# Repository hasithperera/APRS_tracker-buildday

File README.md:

# APRS tracker-build day

- This project is designed as an out reach project under the WVU Amateur radio club - High altitude ballooning grand awarded Fall 2024
- The main goal was to design a system allowing users to send APRS location packets

---
## V1.1 - APRS beacon

- [Build instructions](pcb/README.md) - Partially completed
---
## Bluetooth KISS TNC - v 1.0

- Based on the interest, we added a part 2 for the build day that was developed for advanced users who needed APRS decode capabilities.
- A self powered KISS TNC PCB was designed to carry existing firmware.
	- Initial testing with APRSDroid and YAAC showed promising results
- V1 PCB for the APRS KISS TNC 

---
## Project progress

- November 2024 - Reached out to local clubs on interest and participation
- December 2024 - Basic prototype was tested 
- January 2025 - v1.1 production 
- March 2025 - Software was finalized to allow consistent operation 
- April 2025 - BT KISS TNC v1 PCB added 

*Last edited: April 09 by KE8TJE*

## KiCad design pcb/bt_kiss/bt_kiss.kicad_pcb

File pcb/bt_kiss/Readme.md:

- The Bluetooth KISS TNC implementation schematic and board designs for quick access

## Schematic 

## Program instructions

- Firmware found [here](https://raw.githubusercontent.com/mobilinkd/tnc1/arduino/images/mobilinkd-473-arduino.hex)
- Programming using the com port: `avrdude -c arduino -p m328p -P /dev/ttyUSB1 -b 57600 -U mobilinkd-473-arduino.hex`
- Programming using a USBasp: `avrdude -p m328p -c usbasp -U flash:w:<filename>.hex`

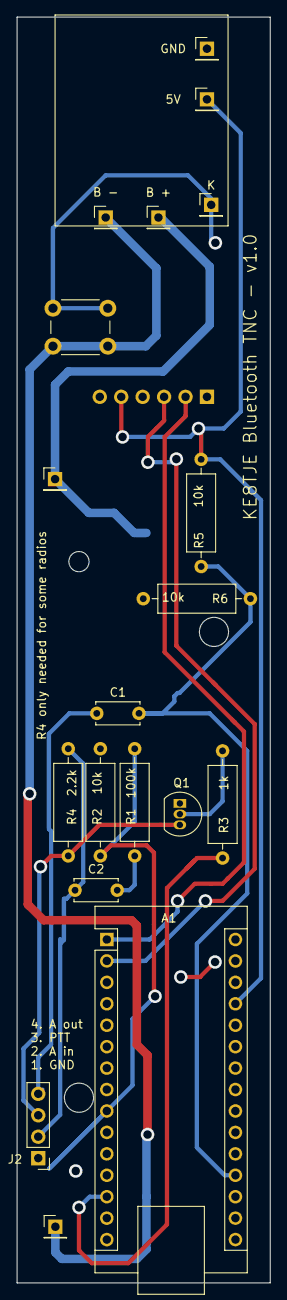
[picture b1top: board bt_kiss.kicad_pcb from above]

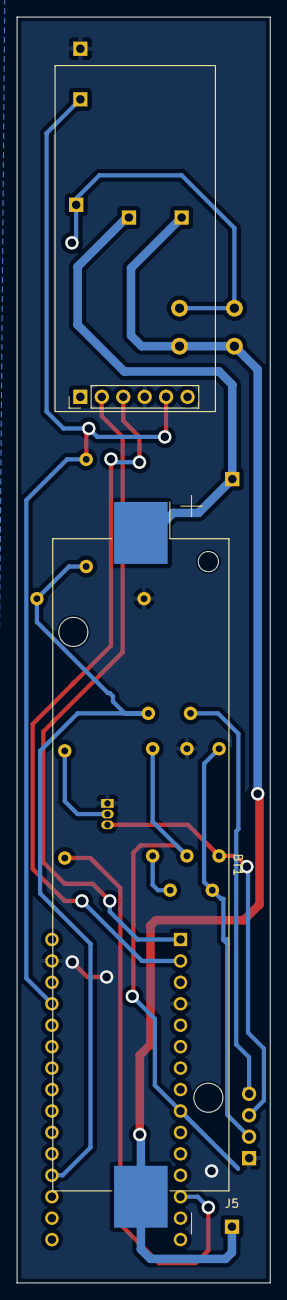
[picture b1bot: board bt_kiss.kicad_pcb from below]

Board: 2 copper layers, 30.0 x 150.0 mm, 21 parts (2 on the bottom side), 15 nets.

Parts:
5V: 5V; PinHeader_1x01_P2.54mm_Vertical
A1: Arduino_Nano_v3.x; Arduino_Nano
B +: Bat_Plus; PinHeader_1x01_P2.54mm_Vertical
B -: Bat_GND; PinHeader_1x01_P2.54mm_Vertical
BT1: Battery_Cell; BatteryHolder_Keystone_1042_1x18650
C1: 10nf; C_Disc_D5.0mm_W2.5mm_P5.00mm
C2: 100nf; C_Disc_D5.0mm_W2.5mm_P5.00mm
GND: GND; PinHeader_1x01_P2.54mm_Vertical
J1: HC-05; PinHeader_1x06_P2.54mm_Vertical
J2: to_radio; PinHeader_1x04_P2.54mm_Vertical
J4: Bat_Plus; PinHeader_1x01_P2.54mm_Vertical
J5: Bat_GND; PinHeader_1x01_P2.54mm_Vertical
K: Key; PinHeader_1x01_P2.54mm_Vertical
Q1: PN2222A; TO-92_Inline
R1: 100k; R_Axial_DIN0309_L9.0mm_D3.2mm_P12.70mm_Horizontal
R2, R5, R6: 10k; R_Axial_DIN0309_L9.0mm_D3.2mm_P12.70mm_Horizontal
R3: 1k; R_Axial_DIN0309_L9.0mm_D3.2mm_P12.70mm_Horizontal
R4: 2.2k; R_Axial_DIN0309_L9.0mm_D3.2mm_P12.70mm_Horizontal
SW1: SW_Push; SW_PUSH_6mm

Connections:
GND: A1.4 (GND), A1.29 (GND), GND.1, J1.4, J2.1, Q1.1 (E), R2.2, R6.2
unnamed: A1.19 (A0), C1.2, R5.2, R6.1
unnamed: A1.2 (D0/RX), J1.3
unnamed: A1.1 (D1/TX), J1.2
unnamed: A1.9 (D6), R1.1, R2.1
unnamed: A1.13 (D10), R3.1
unnamed: B +.1, BT1.1 (+), J4.1
unnamed: B -.1, BT1.2 (-), J5.1, SW1.2
unnamed: C2.2, R1.2
unnamed: K.1, SW1.1
unnamed: Q1.2 (B), R3.2
PTT: J2.3, Q1.3 (C), R4.1
VCC: 5V.1, A1.27 (+5V), J1.5, R5.1
audio_in: C2.1, J2.2, R4.2
audio_out: C1.1, J2.4

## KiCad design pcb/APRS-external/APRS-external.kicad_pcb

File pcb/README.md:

# PCB Design updates 

## V1.1 

---
## Build guide 

- Follow the component list below and populate the PCB with components 
- Note 2 changes:
	- the 2N2222 needs to be replaced by a BS170 MOSFET
	- Bridge the Pins **D2** and **D3** on the Arduino
- Once you have every thing soldered in connect power via the USB C connector
	- You should see the power led light up on the arduino
	- Power led on the GPS module
- Once you have confirmed power to all the components follow the programming guide 

---
## Component list

| **Symbol** | **Value**    |
| ---------- | ------------ |
| C1         | 100n         |
| C2,C3      | 4.7u         |
| C3,C4      | pol smd      |
| D1         | 1n4001       |
| Q1         | 2N2222/BS170 |
| R1         | 6.2k         |
| R2         | 2k           |
| R3         | 270          |
| R4         | 3.9k         |
| R5         | 1.2k         |
| R6-R8      | 1k           |
| R10        | 2.7k         |
| R11,R12    | 330          |

---
## Program instructions

- Open up the Arduino code provided
- to install the Aprs library go to: Tools > Manage Libraries....
	- Search for `LibAPRS` and install the library by Baris DINC
- Once you have the library installed compile the program and it should compile without errors
- Change `line 45` to add your call
### Basic radio interface testing

- Once the Arduino is properly programmed on power on the Radio will be keyed up 2 times as a test. 
	- If this step fails: check your connectors and check your MOSFET.
- To test the system indoors without GPS lock uncomment `line 30`, this will enable a simulate mode where GPS data is being. artificially provided 
- Once the second count reaches the value set in `APRS_TX_offset_utc_sec` your radio will transmit an APRS packet.
	- Radio should key down automatically
	- It has been repoted with some radios this may not happen and this was often observed when there was an extended length of cable involved
		- adding a ferrite bead would potentially solve the issue
		- if not using a separate external antenna should help
- NOTE: change the `APRS_TX_offset_utc_sec` to some random value. This is the time your specific APRS unit will transmit. Since its on simplex we don't want every one to TX at the same time. 
- once you have completed testing comment out `line 30` congratulations now you have a working APRS beacon 

if you have questions please reach out to KE8TJE

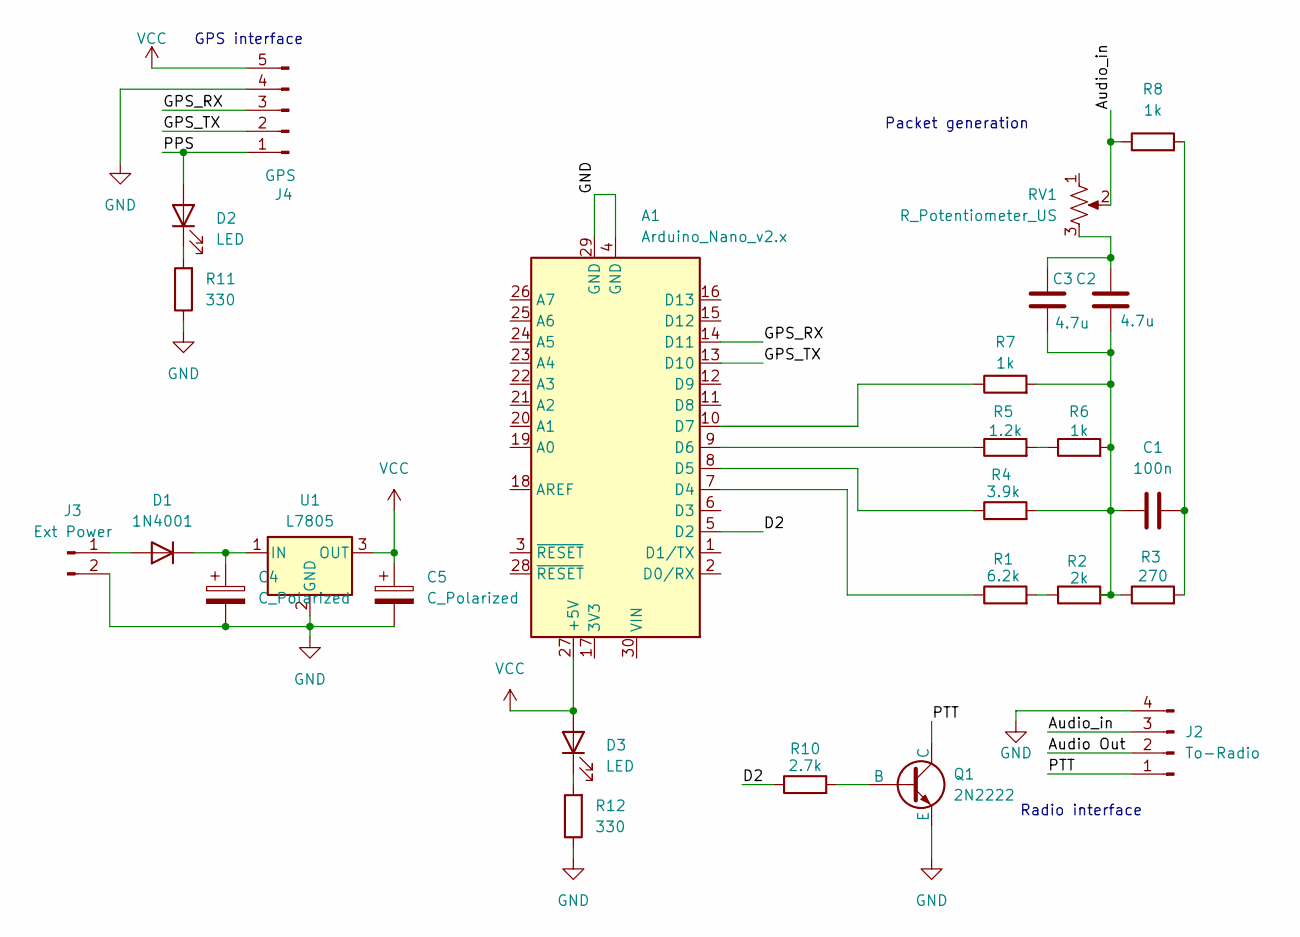
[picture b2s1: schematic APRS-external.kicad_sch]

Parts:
A1: Arduino_Nano_v2.x; Arduino_Nano
C1: 100n; D_0805_2012Metric_Pad1.15x1.40mm_HandSolder
C2, C3: 4.7u; D_0805_2012Metric_Pad1.15x1.40mm_HandSolder
C4, C5: C_Polarized; CP_Elec_4x4.5
D1: 1N4001; D_DO-41_SOD81_P10.16mm_Horizontal
D2, D3: LED; LED_D5.0mm
J2: To-Radio; PinHeader_1x04_P2.54mm_Vertical
J3: Ext Power; PinHeader_1x02_P2.54mm_Vertical
J4: GPS; PinHeader_1x05_P2.54mm_Vertical
Q1: 2N2222; TO-92_Inline_Wide
R1: 6.2k; R_Axial_DIN0207_L6.3mm_D2.5mm_P10.16mm_Horizontal
R2: 2k; R_Axial_DIN0207_L6.3mm_D2.5mm_P10.16mm_Horizontal
R3: 270; R_Axial_DIN0207_L6.3mm_D2.5mm_P10.16mm_Horizontal
R4: 3.9k; R_Axial_DIN0207_L6.3mm_D2.5mm_P10.16mm_Horizontal
R5: 1.2k; R_Axial_DIN0207_L6.3mm_D2.5mm_P10.16mm_Horizontal
R6, R7, R8: 1k; R_Axial_DIN0207_L6.3mm_D2.5mm_P10.16mm_Horizontal
R10: 2.7k; R_Axial_DIN0207_L6.3mm_D2.5mm_P10.16mm_Horizontal
R11, R12: 330; R_Axial_DIN0207_L6.3mm_D2.5mm_P10.16mm_Horizontal
RV1: R_Potentiometer_US; Potentiometer_Piher_PT-10-V05_Vertical
U1: L7805; TO-220-3_Horizontal_TabDown

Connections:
/Audio Out: J2.2
/Audio_in: J2.3, R8.1, RV1.2
/D2: A1.5 (D2), R10.1
/GPS_RX: A1.14 (D11), J4.3
/GPS_TX: A1.13 (D10), J4.2
/PPS: D2.2 (A), J4.1
/PTT: J2.1, Q1.1 (C)
GND: A1.4 (GND), A1.29 (GND), C4.2, C5.2, J2.4, J3.2, J4.4, Q1.3 (E), R11.1, R12.1, U1.2 (GND)
unnamed: A1.7 (D4), R1.1
unnamed: A1.8 (D5), R4.1
unnamed: A1.9 (D6), R5.1
unnamed: A1.10 (D7), R7.1
unnamed: C1.1, C2.1, C3.1, R2.2, R3.1, R4.2, R6.2, R7.2
unnamed: C1.2, R3.2, R8.2
unnamed: C2.2, C3.2, RV1.3
unnamed: D1.2 (A), J3.1
unnamed: C4.1, D1.1 (K), U1.1 (IN)
unnamed: D2.1 (K), R11.2
unnamed: D3.1 (K), R12.2
unnamed: Q1.2 (B), R10.2
unnamed: R1.2, R2.1
unnamed: R5.2, R6.1
VCC: A1.27 (+5V), C5.1, D3.2 (A), J4.5, U1.3 (OUT)

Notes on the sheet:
GPS interface
Packet generation
Radio interface

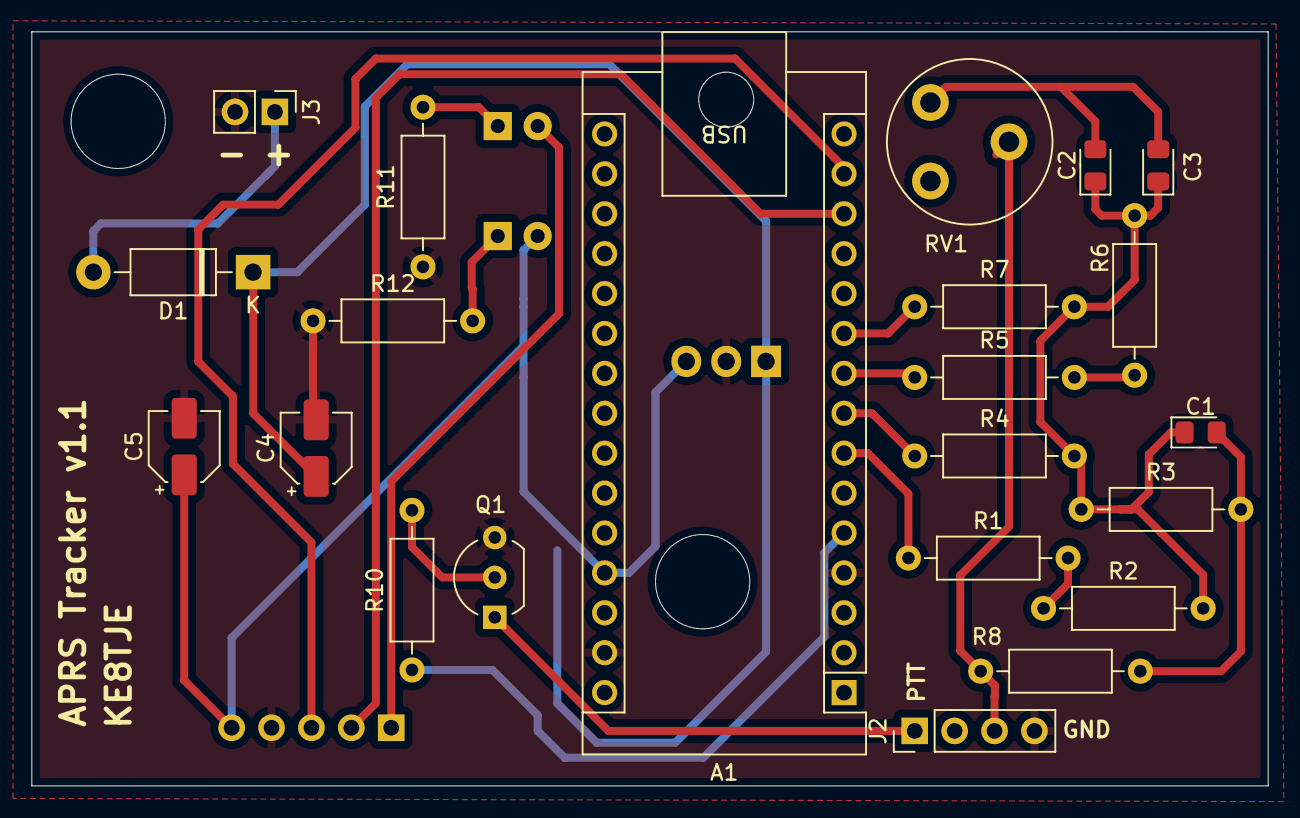
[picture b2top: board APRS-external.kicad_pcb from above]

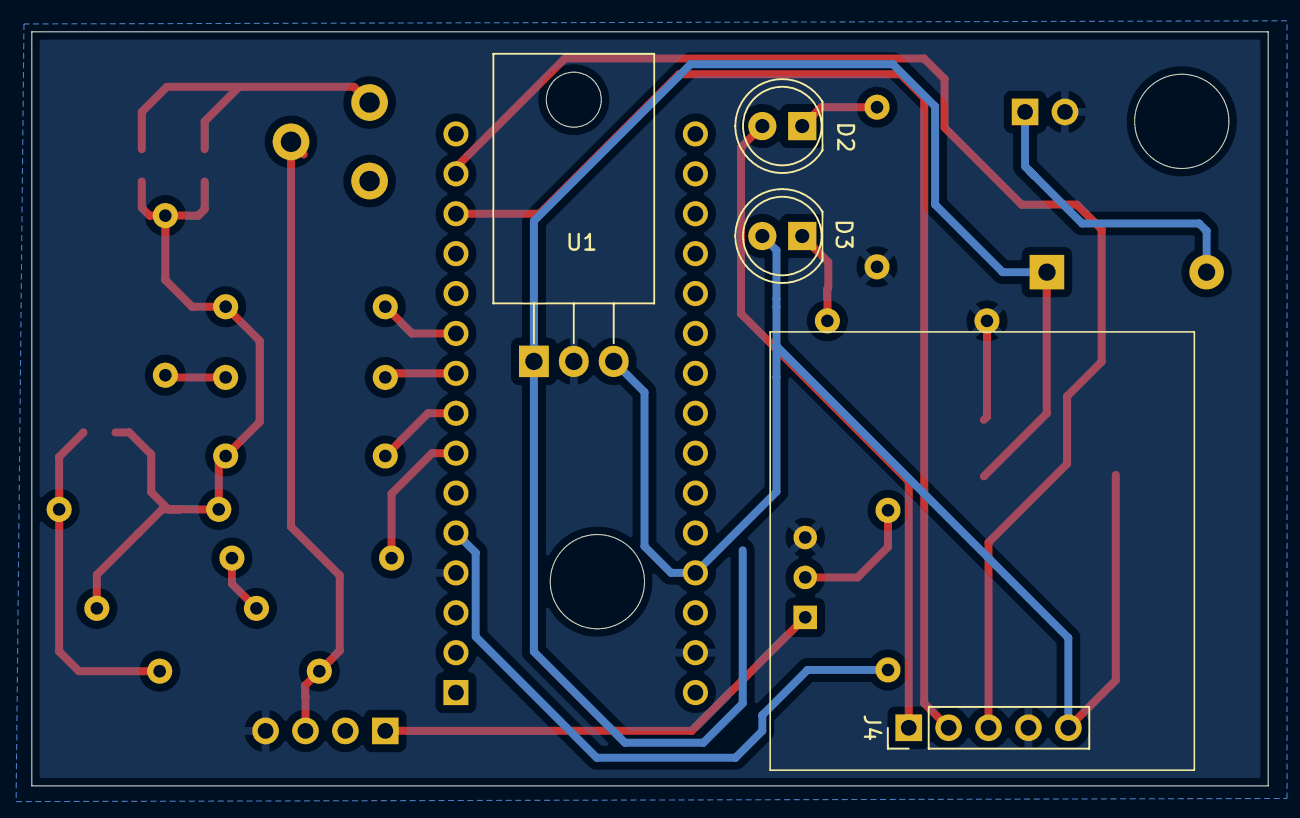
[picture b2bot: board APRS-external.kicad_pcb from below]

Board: 2 copper layers, 78.7 x 48.0 mm, 26 parts (4 on the bottom side), 22 nets.

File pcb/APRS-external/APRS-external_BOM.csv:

"Id";"Designator";"Footprint";"Quantity";"Designation";"Supplier and ref";
1;"R8,R7,R6";"R_Axial_DIN0207_L6.3mm_D2.5mm_P10.16mm_Horizontal";3;"1k";;;
2;"C5,C4";"CP_Elec_4x4.5";2;"C_Polarized";;;
3;"RV1";"Potentiometer_Piher_PT-10-V05_Vertical";1;"R_Potentiometer_US";;;
4;"R11,R12";"R_Axial_DIN0207_L6.3mm_D2.5mm_P10.16mm_Horizontal";2;"330";;;
5;"C2,C3";"D_0805_2012Metric_Pad1.15x1.40mm_HandSolder";2;"4.7u";;;
6;"R10";"R_Axial_DIN0207_L6.3mm_D2.5mm_P10.16mm_Horizontal";1;"2.7k";;;
7;"R1";"R_Axial_DIN0207_L6.3mm_D2.5mm_P10.16mm_Horizontal";1;"6.2k";;;
8;"R4";"R_Axial_DIN0207_L6.3mm_D2.5mm_P10.16mm_Horizontal";1;"3.9k";;;
9;"J3";"PinHeader_1x02_P2.54mm_Vertical";1;"Ext Power";;;
10;"R5";"R_Axial_DIN0207_L6.3mm_D2.5mm_P10.16mm_Horizontal";1;"1.2k";;;
11;"D1";"D_DO-41_SOD81_P10.16mm_Horizontal";1;"1N4001";;;
12;"C1";"D_0805_2012Metric_Pad1.15x1.40mm_HandSolder";1;"100n";;;
13;"A1";"Arduino_Nano";1;"Arduino_Nano_v2.x";;;
14;"R3";"R_Axial_DIN0207_L6.3mm_D2.5mm_P10.16mm_Horizontal";1;"270";;;
15;"J2";"PinHeader_1x04_P2.54mm_Vertical";1;"To-Radio";;;
16;"Q1";"TO-92_Inline_Wide";1;"2N2222";;;
17;"R2";"R_Axial_DIN0207_L6.3mm_D2.5mm_P10.16mm_Horizontal";1;"2k";;;
18;"J4";"PinHeader_1x05_P2.54mm_Vertical";1;"GPS";;;
19;"D3,D2";"LED_D5.0mm";2;"LED";;;
20;"U1";"TO-220-3_Horizontal_TabDown";1;"L7805";;;

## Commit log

2024-12-07 A working version for the public code
2024-12-29 added initial PCB desing
2024-12-29 vault backup: 2024-12-29 17:56:26
2025-01-27 updated boards
2025-01-28 added fixes for physical constraints on the GPS
2025-01-28 updated silk screen print locations
2025-01-28 added project label
2025-01-28 vault backup: 2025-01-28 11:10:10
2025-01-28 vault backup: 2025-01-28 11:10:58
2025-02-18 added BOM and final version made with JLC
2025-03-12 added lib aprs removed all the unused code from old projects
2025-03-12 added GPS time sync and new triggers for APRS packet
2025-03-13 fixed aprs packet wait
2025-03-24 added sim posiblity maintaining time triggers
2025-04-06 added BT KISS TNC PCB
2025-04-07 added 18650 battery holder for the BT KISS TNC PCB
2025-04-07 added KISS TNC read me: 2025-04-07 18:54:28
2025-04-07 vault backup: 2025-04-07 18:56:54
2025-04-08 BT TNC v1.1 added ready for production
2025-04-10 vault backup: 2025-04-09 21:49:10
2025-04-10 vault backup: 2025-04-10 00:00:35
2025-04-11 vault backup: 2025-04-10 23:21:52
2025-04-11 vault backup: 2025-04-11 09:08:07
2025-04-29 Update APRS_build-day.ino
    Removed telemetry from the default code and added comments for advanced users
2025-06-03 added sim mode comments
